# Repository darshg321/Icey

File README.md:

# Icey

an Uno-sized FPGA iCE40-UP5K board for learning!

<video src="https://github.com/darshg321/Icey/raw/main/assets/DEMO.mp4" controls width="100%"></video>

*conway's game of life running on icey, 128 cells computed every clock! ([video](assets/DEMO.mp4))*

it features:
- integrated VGA connector with display out
- integrated USB peripheral support (such as keyboards!)
- programming with usb C via JTAG or UART
- QSPI flash
- micro SD card
- header pins broken out for extra features
- LEDs
- buttons

# Learn

A project-based Verilog course built around this board, with a Verilog compiler, simulator and the iCE40 toolchain running in your browser: [`learn/`](learn/README.md). It goes from lighting an LED to building a CPU and an Apple I.

```sh
cd learn && npm install && npm run dev
```

# Firmware

tools, examples and bring-up notes are in [`firmware/`](firmware/README.md). to run the demo:

```sh
git clone --recurse-submodules https://github.com/darshg321/Icey && cd Icey
./firmware/life-demo.sh
```

# PCB

# Schematic

## Headers

| Pin | Net | FPGA |
|---|---|---|
| 1 | `IOT_42b` | `31` |
| 2 | `IOT_43a` | `32` |
| 3 | `IOT_44b` | `34` |
| 4 | `IOT_46b_G0` | `35` |
| 5 | `IOT_48b` | `36` |
| 6 | `IOT_45a_G1` | `37` |
| 7 | `IOT_50b` | `38` |
| 8 | `IOT_51a` | `42` |
| 9 | `IOT_49a` | `43` |
| 10 | GND | — |
| 11 | +3V3 | — |
| 12 | VBUS (+5V) | — |

### Configuration SPI

| Pin | Net | | Pin | Net |
|---|---|---|---|---|
| 1 | `CS` | | 5 | `FLASH_WP` |
| 2 | `SCK` | | 6 | `FLASH_HOLD` |
| 3 | `MOSI` | | 7 | **+3V3** |
| 4 | `MISO` | | 8 | **GND** |

# BOM

| Item     | Qty | Price (USD)  |
|----------|-----|--------------|
| PCB      | 5   | 7.00         |
| Assembly | 2   | 106.51       |

### Contact
email me at darshg321 (@) gmail.com :)

### this project is open source certified at https://certification.oshwa.org/ca000078.html

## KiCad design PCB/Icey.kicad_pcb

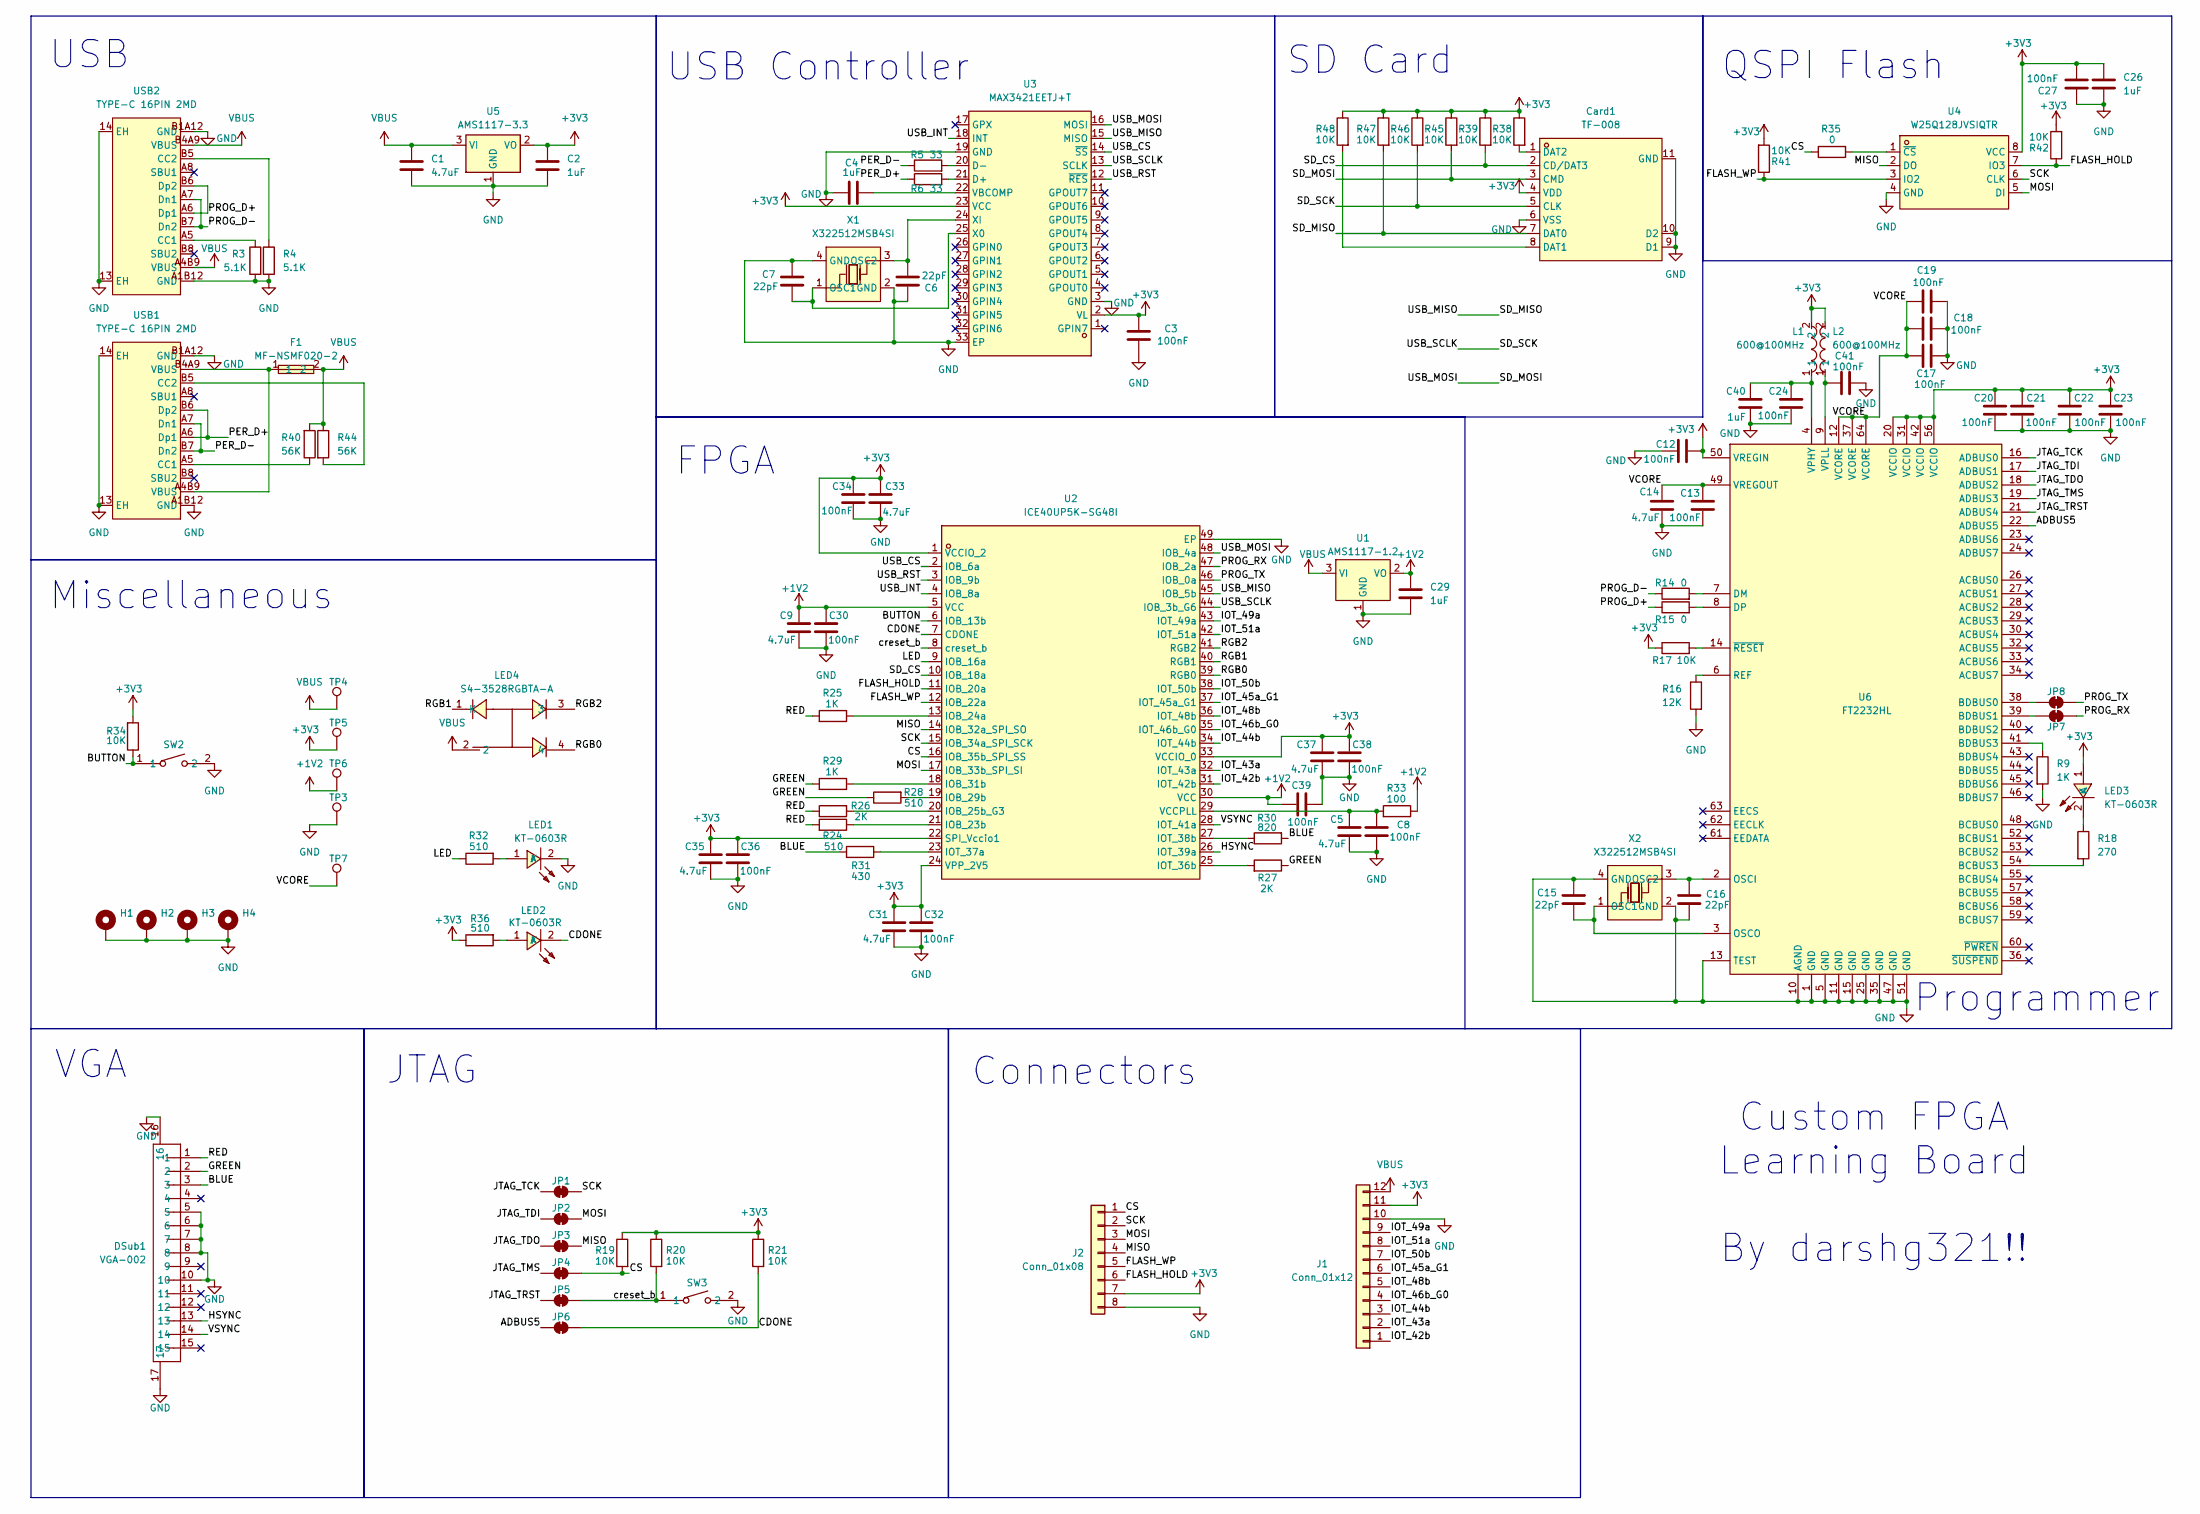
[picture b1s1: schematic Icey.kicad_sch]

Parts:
C1, C5, C9, C14, C31, C33, C35, C37: 4.7uF; C_0805_2012Metric
C2, C4, C26, C29, C40: 1uF; C_0603_1608Metric
C3, C8, C12, C13, C17, C18, C19, C20, C21, C22, C23, C24, C27, C30, C32, C34, C36, C38, C39, C41: 100nF; C_0603_1608Metric
C6, C7, C15, C16: 22pF; C_0603_1608Metric
Card1: TF-008; TF-SMD_TF-008; MPN TF-008; LCSC Part C428465
DSub1: VGA-002; D-SUB-TH_VGA-002; MPN VGA-002; LCSC Part C138387
F1: MF-NSMF020-2; F1206; MPN MF-NSMF020-2; LCSC Part C185112
H1, H2, H3, H4: MountingHole_Pad; MountingHole_3.2mm_M3_Pad_Via
J1: Conn_01x12; PinHeader_1x12_P2.54mm_Vertical
J2: Conn_01x08; PinHeader_1x08_P2.54mm_Vertical
JP1, JP2, JP3, JP4, JP5, JP6, JP7, JP8: SolderJumper_2_Bridged; SolderJumper-2_P1.3mm_Bridged_RoundedPad1.0x1.5mm
L1, L2: 600@100MHz; L0805; MPN GZ2012D601TF; LCSC Part C1017
LED1, LED2, LED3: KT-0603R; LED-SMD_L1.6-W0.8-R-RD; MPN KT-0603R; LCSC Part C2286
LED4: S4-3528RGBTA-A; LED-SMD_4P-L3.2-W2.8-LS3.5-TL-1; MPN S4-3528RGBTA-A; LCSC Part C2827321
R3, R4: 5.1K; R_0603_1608Metric
R5, R6: 33; R_0603_1608Metric
R9, R25, R29: 1K; R_0603_1608Metric
R14, R15, R35: 0; R_0603_1608Metric
R16: 12K; R_0603_1608Metric
R17, R19, R20, R21, R34, R38, R39, R41, R42, R45, R46, R47, R48: 10K; R_0603_1608Metric
R18: 270; R_0603_1608Metric
R24, R28, R32, R36: 510; R_0603_1608Metric
R26, R27: 2K; R_0603_1608Metric
R30: 820; R_0603_1608Metric
R31: 430; R_0603_1608Metric
R33: 100; R_0603_1608Metric
R40, R44: 56K; R_0603_1608Metric
SW2, SW3: TS-1088-AR02016; SW-SMD_L3.9-W3.0-P4.45; MPN TS-1088-AR02016; LCSC Part C720477
TP3, TP4, TP5, TP6, TP7: TestPoint; TestPoint_Pad_D2.0mm
U1: AMS1117-1.2; SOT-223-3_TabPin2; MPN AMS1117-1.2; LCSC Part C347218
U2: ICE40UP5K-SG48I; QFN-48_L7.0-W7.0-P0.50-TL-EP5.4-1; MPN ICE40UP5K-SG48I; LCSC Part C2678152
U3: MAX3421EETJ+T; VQFN-32_L5.0-W5.0-P0.50-BL-EP3.2; MPN MAX3421EETJ+T; LCSC Part C1870151
U4: W25Q128JVSIQTR; SOIC-8_L5.3-W5.3-P1.27-LS8.0-BL; MPN W25Q128JVSIQ; LCSC Part C97521
U5: AMS1117-3.3; SOT-223-3_TabPin2
U6: FT2232HL; LQFP-64_L10.0-W10.0-P0.50-LS12.0-TL; MPN FT2232HL-REEL; LCSC Part C27882
USB1, USB2: TYPE-C 16PIN 2MD; USB-C-SMD_TYPE-C-16PIN-2MD-073; MPN TYPE-C 16PIN 2MD(073); LCSC Part C2765186
X1, X2: X322512MSB4SI; CRYSTAL-SMD_4P-L3.2-W2.5-BL; MPN X322512MSB4SI; LCSC Part C9002

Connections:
+1V2: C9.2, C29.1, C30.2, C39.2, R33.1, TP6.1, U1.2 (VO), U2.5 (VCC), U2.30 (VCC)
+3V3: C2.1, C3.2, C12.1, C20.1, C21.2, C22.2, C23.2, C26.1, C27.1, C31.2, C32.2, C33.1, C34.1, C35.2, C36.2, C37.2, C38.2, Card1.4 (VDD), J1.11, J2.7, L1.2, L2.2, LED3.1 (A), R17.1, R19.1, R20.1, R21.1, R34.2, R36.1, R38.1, R39.1, R41.2, R42.2, R45.1, R46.1, R47.1, R48.1, TP5.1, U2.1 (VCCIO_2), U2.22 (SPI_Vccio1), U2.24 (VPP_2V5), U2.33 (VCCIO_0), U3.2 (VL), U3.23 (VCC), U4.8 (VCC), U5.2 (VO), U6.20 (VCCIO), U6.31 (VCCIO), U6.42 (VCCIO), U6.50 (VREGIN), U6.56 (VCCIO)
/ADBUS5: JP6.1 (A), U6.22 (ADBUS5)
/BLUE: DSub1.3, R30.2, R31.2
/BUTTON: R34.1, SW2.1, U2.6 (IOB_13b)
/CDONE: JP6.2 (B), LED2.2 (K), R21.2, U2.7 (CDONE)
/CS: J2.1, JP4.2 (B), R19.2, R35.1, U2.16 (IOB_35b_SPI_SS)
/FLASH_HOLD: J2.6, R42.1, U2.11 (IOB_20a), U4.7 (IO3)
/FLASH_WP: J2.5, R41.1, U2.12 (IOB_22a), U4.3 (IO2)
/GREEN: DSub1.2, R27.1, R28.1, R29.2
/HSYNC: DSub1.13, U2.26 (IOT_39a)
/IOT_42b: J1.1, U2.31 (IOT_42b)
/IOT_43a: J1.2, U2.32 (IOT_43a)
/IOT_44b: J1.3, U2.34 (IOT_44b)
/IOT_45a_G1: J1.6, U2.37 (IOT_45a_G1)
/IOT_46b_G0: J1.4, U2.35 (IOT_46b_G0)
/IOT_48b: J1.5, U2.36 (IOT_48b)
/IOT_49a: J1.9, U2.43 (IOT_49a)
/IOT_50b: J1.7, U2.38 (IOT_50b)
/IOT_51a: J1.8, U2.42 (IOT_51a)
/JTAG_TCK: JP1.1 (A), U6.16 (ADBUS0)
/JTAG_TDI: JP2.1 (A), U6.17 (ADBUS1)
/JTAG_TDO: JP3.1 (A), U6.18 (ADBUS2)
/JTAG_TMS: JP4.1 (A), U6.19 (ADBUS3)
/JTAG_TRST: JP5.1 (A), U6.21 (ADBUS4)
/LED: R32.1, U2.9 (IOB_16a)
/MISO: J2.4, JP3.2 (B), U2.14 (IOB_32a_SPI_SO), U4.2 (DO)
/MOSI: J2.3, JP2.2 (B), U2.17 (IOB_33b_SPI_SI), U4.5 (DI)
/PER_D+: R6.1, USB1.A6 (Dp1), USB1.B6 (Dp2)
/PER_D-: R5.1, USB1.A7 (Dn1), USB1.B7 (Dn2)
/PROG_D+: R15.1, USB2.A6 (Dp1), USB2.B6 (Dp2)
/PROG_D-: R14.1, USB2.A7 (Dn1), USB2.B7 (Dn2)
/PROG_RX: JP7.1 (A), U2.47 (IOB_2a)
/PROG_TX: JP8.2 (B), U2.46 (IOB_0a)
/RED: DSub1.1, R24.2, R25.2, R26.1
/RGB0: LED4.4, U2.39 (RGB0)
/RGB1: LED4.1 (K), U2.40 (RGB1)
/RGB2: LED4.3, U2.41 (RGB2)
/SCK: J2.2, JP1.2 (B), U2.15 (IOB_34a_SPI_SCK), U4.6 (CLK)
/SD_CS: Card1.2 (CD/DAT3), R39.2, U2.10 (IOB_18a)
/SD_MISO: Card1.7 (DAT0), R47.2, U2.45 (IOB_5b), U3.15 (MISO)
/SD_MOSI: Card1.3 (CMD), R45.2, U2.48 (IOB_4a), U3.16 (MOSI)
/SD_SCK: Card1.5 (CLK), R46.2, U2.44 (IOB_3b_G6), U3.13 (SCLK)
/USB_CS: U2.2 (IOB_6a), U3.14 (~SS)
/USB_INT: U2.4 (IOB_8a), U3.18 (INT)
/USB_RST: U2.3 (IOB_9b), U3.12 (~RES)
/VCORE: C13.1, C14.1, C17.1, C18.2, C19.2, TP7.1, U6.12 (VCORE), U6.37 (VCORE), U6.49 (VREGOUT), U6.64 (VCORE)
/VSYNC: DSub1.14, U2.28 (IOT_41a)
/creset_b: JP5.2 (B), R20.2, SW3.1, U2.8 (creset_b)
GND: C1.2, C2.2, C3.1, C4.1, C5.1, C6.2, C7.2, C8.1, C9.1, C12.2, C13.2, C14.2, C15.2, C16.2, C17.2, C18.1, C19.1, C20.2, C21.1, C22.1, C23.1, C24.2, C26.2, C27.2, C29.2, C30.1, C31.1, C32.1, C33.2, C34.2, C35.1, C36.1, C37.1, C38.1, C39.1, C40.1, C41.2, Card1.6 (VSS), Card1.9 (D1), Card1.10 (D2), Card1.11 (GND), DSub1.5, DSub1.6, DSub1.7, DSub1.8, DSub1.10, DSub1.16, DSub1.17, H1.1, H2.1, H3.1, H4.1, J1.10, J2.8, LED1.2 (K), R3.2, R4.2, R9.2, R16.2, SW2.2, SW3.2, TP3.1, U1.1 (GND), U2.49 (EP), U3.3 (GND), U3.19 (GND), U3.33 (EP), U4.4 (GND), U5.1 (GND), U6.1 (GND), U6.5 (GND), U6.10 (AGND), U6.11 (GND), U6.13 (TEST), U6.15 (GND), U6.25 (GND), U6.35 (GND), U6.47 (GND), U6.51 (GND), USB1.13 (EH), USB1.14 (EH), USB1.A1B12 (GND), USB1.B1A12 (GND), USB2.13 (EH), USB2.14 (EH), USB2.A1B12 (GND), USB2.B1A12 (GND), X1.2 (GND), X1.4 (GND), X2.2 (GND), X2.4 (GND)
unnamed: Card1.8 (DAT1), R48.2
unnamed: Card1.1 (DAT2), R38.2
unnamed: F1.1, USB1.A4B9 (VBUS), USB1.B4A9 (VBUS)
unnamed: JP7.2 (B), U6.39 (BDBUS1)
unnamed: JP8.1 (A), U6.38 (BDBUS0)
unnamed: LED1.1 (A), R32.2
unnamed: LED2.1 (A), R36.2
unnamed: LED3.2 (K), R18.1
unnamed: R24.1, U2.21 (IOB_23b)
unnamed: R25.1, U2.13 (IOB_24a)
unnamed: R26.2, U2.20 (IOB_25b_G3)
unnamed: R28.2, U2.19 (IOB_29b)
unnamed: R29.1, U2.18 (IOB_31b)
unnamed: R27.2, U2.25 (IOT_36b)
unnamed: R31.1, U2.23 (IOT_37a)
unnamed: R30.1, U2.27 (IOT_38b)
unnamed: C5.2, C8.2, R33.2, U2.29 (VCCPLL)
unnamed: R6.2, U3.21 (D+)
unnamed: R5.2, U3.20 (D-)
unnamed: C4.2, U3.22 (VBCOMP)
unnamed: C7.1, U3.25 (X0), X1.1 (OSC1)
unnamed: C6.1, U3.24 (XI), X1.3 (OSC2)
unnamed: R35.2, U4.1 (~CS)
unnamed: R18.2, U6.54 (BCBUS3)
unnamed: R9.1, U6.41 (BDBUS3)
unnamed: R14.2, U6.7 (DM)
unnamed: R15.2, U6.8 (DP)
unnamed: C16.1, U6.2 (OSCI), X2.3 (OSC2)
unnamed: C15.1, U6.3 (OSCO), X2.1 (OSC1)
unnamed: R16.1, U6.6 (REF)
unnamed: C24.1, C40.2, L1.1, U6.4 (VPHY)
unnamed: C41.1, L2.1, U6.9 (VPLL)
unnamed: R17.2, U6.14 (~RESET)
unnamed: R40.1, USB1.A5 (CC1)
unnamed: R44.2, USB1.B5 (CC2)
unnamed: R3.1, USB2.A5 (CC1)
unnamed: R4.1, USB2.B5 (CC2)
VBUS: C1.1, F1.2, J1.12, LED4.2, R40.2, R44.1, TP4.1, U1.3 (VI), U5.3 (VI), USB2.A4B9 (VBUS), USB2.B4A9 (VBUS)

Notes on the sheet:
QSPI Flash
USB Controller
VGA
Custom FPGA Learning Board By darshg321!!
Connectors
FPGA
USB
JTAG
Programmer
SD Card
Miscellaneous

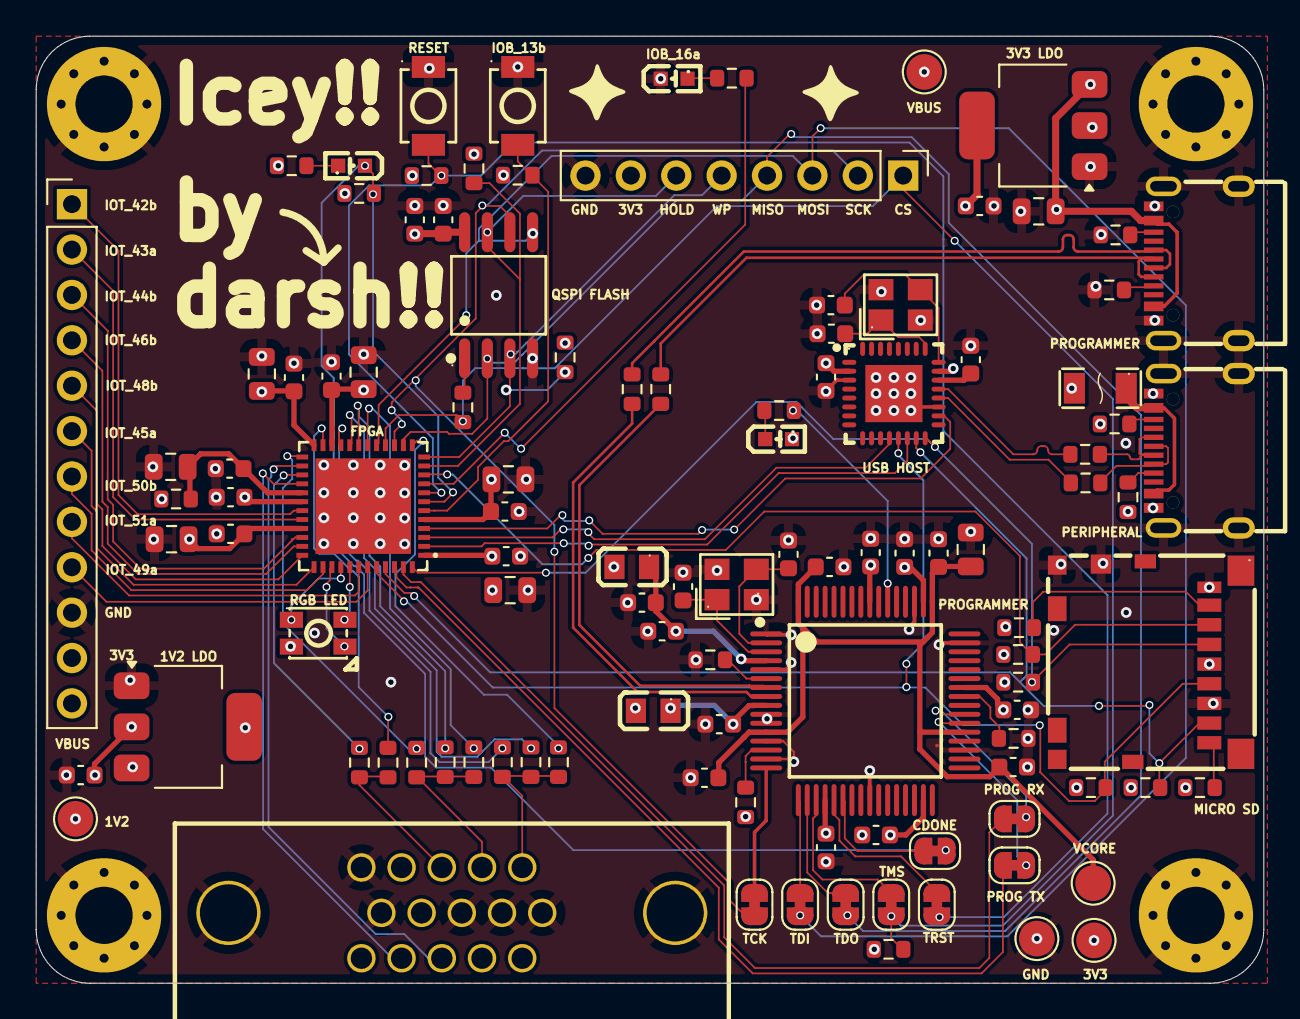
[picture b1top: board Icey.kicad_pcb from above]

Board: 4 copper layers, 68.7 x 53.0 mm, 113 parts (0 on the bottom side), 88 nets.

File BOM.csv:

"Reference","Value","Footprint","Datasheet","Qty","DNP","Exclude from BOM","Exclude from Board"
"C1,C5,C9,C14,C31,C33,C35,C37","4.7uF","Capacitor_SMD:C_0805_2012Metric","~","8","","",""
"C2,C4,C26,C29,C40","1uF","Capacitor_SMD:C_0603_1608Metric","~","5","","",""
"C3,C8,C12,C13,C17,C18,C19,C20,C21,C22,C23,C24,C27,C30,C32,C34,C36,C38,C39,C41","100nF","Capacitor_SMD:C_0603_1608Metric","~","20","","",""
"C6,C7,C15,C16","22pF","Capacitor_SMD:C_0603_1608Metric","~","4","","",""
"Card1","TF-008","easyeda2kicad:TF-SMD_TF-008","https://www.lcsc.com/datasheet/C428465.pdf","1","","",""
"D1","SS14","easyeda2kicad:SMA_L4.2-W2.6-LS5.0-RD_1","https://lcsc.com/product-detail/Schottky-Barrier-Diodes-SBD_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","1","","",""
"DSub1","VGA-002","easyeda2kicad:D-SUB-TH_VGA-002","https://lcsc.com/product-detail/D-Sub-Connectors_VGA-002_C13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","1","","",""
"F1","MF-NSMF020-2","easyeda2kicad:F1206","https://lcsc.com/product-detail/Surface-Mount-Fuses_BOURNS_M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","1","","",""
"H1,H2,H3,H4","MountingHole_Pad","MountingHole:MountingHole_3.2mm_M3_Pad_Via","~","4","","Excluded from BOM",""
"J1","Conn_01x12","Connector_PinHeader_2.54mm:PinHeader_1x12_P2.54mm_Vertical","~","1","","",""
"J2","Conn_01x08","Connector_PinHeader_2.54mm:PinHeader_1x08_P2.54mm_Vertical","~","1","","",""
"JP1,JP2,JP3,JP4,JP5,JP6,JP7,JP8","SolderJumper_2_Bridged","Jumper:SolderJumper-2_P1.3mm_Bridged_RoundedPad1.0x1.5mm","~","8","","Excluded from BOM",""
"L1,L2","600@100MHz","easyeda2kicad:L0805","https://lcsc.com/product-detail/Ferrite-Beads-And-Chips_600R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","2","","",""
"LED1,LED2,LED3","KT-0603R","easyeda2kicad:LED-SMD_L1.6-W0.8-R-RD","https://lcsc.com/product-detail/Light-Emitting-Diodes-LED_Re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","3","","",""
"R3,R4","5.1K","Capacitor_SMD:C_0603_1608Metric","~","2","","",""
"R5,R6","33","Capacitor_SMD:C_0603_1608Metric","~","2","","",""
"R9,R25,R29","1K","Capacitor_SMD:C_0603_1608Metric","~","3","","",""
"R14,R15,R35,R41,R42,R43","0","Capacitor_SMD:C_0603_1608Metric","~","6","","",""
"R16","12K","Capacitor_SMD:C_0603_1608Metric","~","1","","",""
"R17,R19,R20,R21,R34,R38,R39,R45,R46,R47,R48","10K","Capacitor_SMD:C_0603_1608Metric","~","11","","",""
"R18","270","Capacitor_SMD:C_0603_1608Metric","~","1","","",""
"R24,R28,R32,R36","510","Capacitor_SMD:C_0603_1608Metric","~","4","","",""
"R26,R27","2K","Capacitor_SMD:C_0603_1608Metric","~","2","","",""
"R30","820","Capacitor_SMD:C_0603_1608Metric","~","1","","",""
"R31","430","Capacitor_SMD:C_0603_1608Metric","~","1","","",""
"R33","100","Capacitor_SMD:C_0603_1608Metric","~","1","","",""
"R40,R44","56K","Capacitor_SMD:C_0603_1608Metric","~","2","","",""
"SW2,SW3","TS-1088-AR02016","easyeda2kicad:SW-SMD_L3.9-W3.0-P4.45","https://lcsc.com/product-detail/Tactile-Switches_XUNPU-TS-10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","2","","",""
"TP3,TP4,TP5,TP6","TestPoint","TestPoint:TestPoint_Pad_D2.0mm","~","4","","",""
"U1","AMS1117-1.2","Package_TO_SOT_SMD:SOT-223-3_TabPin2","https://lcsc.com/product-detail/Others_Youtai-Semiconductor-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","1","","",""
"U2","ICE40UP5K-SG48I","easyeda2kicad:QFN-48_L7.0-W7.0-P0.50-TL-EP5.4-1","https://www.lcsc.com/datasheet/C2678152.pdf","1","","",""
"U3","MAX3421EETJ+T","easyeda2kicad:VQFN-32_L5.0-W5.0-P0.50-BL-EP3.2","https://www.lcsc.com/datasheet/C1870151.pdf","1","","",""
"U4","W25Q128JVSIQTR","easyeda2kicad:SOIC-8_L5.3-W5.3-P1.27-LS8.0-BL","https://lcsc.com/product-detail/FLASH_W25Q128JVSIQTR_C97521.html","1","","",""
"U5","AMS1117-3.3","Package_TO_SOT_SMD:SOT-223-3_TabPin2","http://www.advanced-monolithic.com/pdf/ds1117.pdf","1","","",""
"U6","FT2232HL","easyeda2kicad:LQFP-64_L10.0-W10.0-P0.50-LS12.0-TL","https://lcsc.com/product-detail/USB_FTDI_FT2232HL_FT2232HL_C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","1","","",""
"U8","FM-B2020RGBA-HG_C42421005","easyeda2kicad:LED-SMD_FM-B2020RGBA-HG","https://www.lcsc.com/datasheet/C42421005.pdf","1","","",""
"USB1,USB2","TYPE-C 16PIN 2MD","easyeda2kicad:USB-C-SMD_TYPE-C-16PIN-2MD-073","https://www.lcsc.com/datasheet/C2765186.pdf","2","","",""
"X1,X2","X322512MSB4SI","easyeda2kicad:CRYSTAL-SMD_4P-L3.2-W2.5-BL","https://lcsc.com/product-detail/SMD-Crystals_YSX321SL-12MHZ-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","2","","",""

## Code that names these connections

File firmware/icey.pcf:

# Icey (rev 1) - iCE40UP5K-SG48 pin constraints
# Every line uses -nowarn, so a design only needs to declare the ports it uses.
# There is NO external clock: use SB_HFOSC (see examples/), or feed one into P4.

# ---- LEDs / button -------------------------------------------------------
set_io -nowarn LED        9    # LED1, active high
set_io -nowarn BTN        6    # SW2, active low (10k pull-up)
set_io -nowarn RGB0       39   # LED4 red,   open-drain, active low (anode on 5V)
set_io -nowarn RGB1       40   # LED4 blue   (drive with SB_RGBA_DRV or a plain output)
set_io -nowarn RGB2       41   # LED4 green

# ---- UART to PC (FT2232H channel B, /dev/ttyUSB1) -------------------------
set_io -nowarn RX         46   # PC -> FPGA  (net PROG_TX)
set_io -nowarn TX         47   # FPGA -> PC  (net PROG_RX)

# ---- VGA (resistor DAC: 3-bit R/G, 2-bit B) -------------------------------
set_io -nowarn HSYNC      26
set_io -nowarn VSYNC      28
set_io -nowarn VGA_R[2]   21   # 510R (MSB)
set_io -nowarn VGA_R[1]   13   # 1k
set_io -nowarn VGA_R[0]   20   # 2k   (LSB)
set_io -nowarn VGA_G[2]   19   # 510R (MSB)
set_io -nowarn VGA_G[1]   18   # 1k
set_io -nowarn VGA_G[0]   25   # 2k   (LSB)
set_io -nowarn VGA_B[1]   23   # 430R (MSB)
set_io -nowarn VGA_B[0]   27   # 820R (LSB)

# ---- Shared SPI bus: micro SD card + MAX3421E USB host ---------------------
set_io -nowarn SD_SCK     44
set_io -nowarn SD_MOSI    48
set_io -nowarn SD_MISO    45
set_io -nowarn SD_CS      10
set_io -nowarn USB_CS     2    # MAX3421E SS#
set_io -nowarn USB_RST    3    # MAX3421E RES# (active low)
set_io -nowarn USB_INT    4    # MAX3421E INT

# ---- SPI flash (W25Q128JV) from user logic --------------------------------
# NOTE: rev-1 board crosses the data lines relative to the FPGA's SPI_SO/SPI_SI
# names. From user logic these assignments are correct (verified on hardware).
set_io -nowarn FLASH_SCK  15
set_io -nowarn FLASH_CS   16
set_io -nowarn FLASH_MOSI 17   # FPGA -> flash DI
set_io -nowarn FLASH_MISO 14   # flash DO -> FPGA
set_io -nowarn FLASH_WP   12   # IO2 for quad mode
set_io -nowarn FLASH_HOLD 11   # IO3 for quad mode

# ---- Header J1 (pin 10 GND, 11 +3V3, 12 VBUS) -----------------------------
set_io -nowarn P1         31
set_io -nowarn P2         32
set_io -nowarn P3         34
set_io -nowarn P4         35   # global buffer G0 - external clock input
set_io -nowarn P5         36
set_io -nowarn P6         37   # global buffer G1
set_io -nowarn P7         38
set_io -nowarn P8         42
set_io -nowarn P9         43
